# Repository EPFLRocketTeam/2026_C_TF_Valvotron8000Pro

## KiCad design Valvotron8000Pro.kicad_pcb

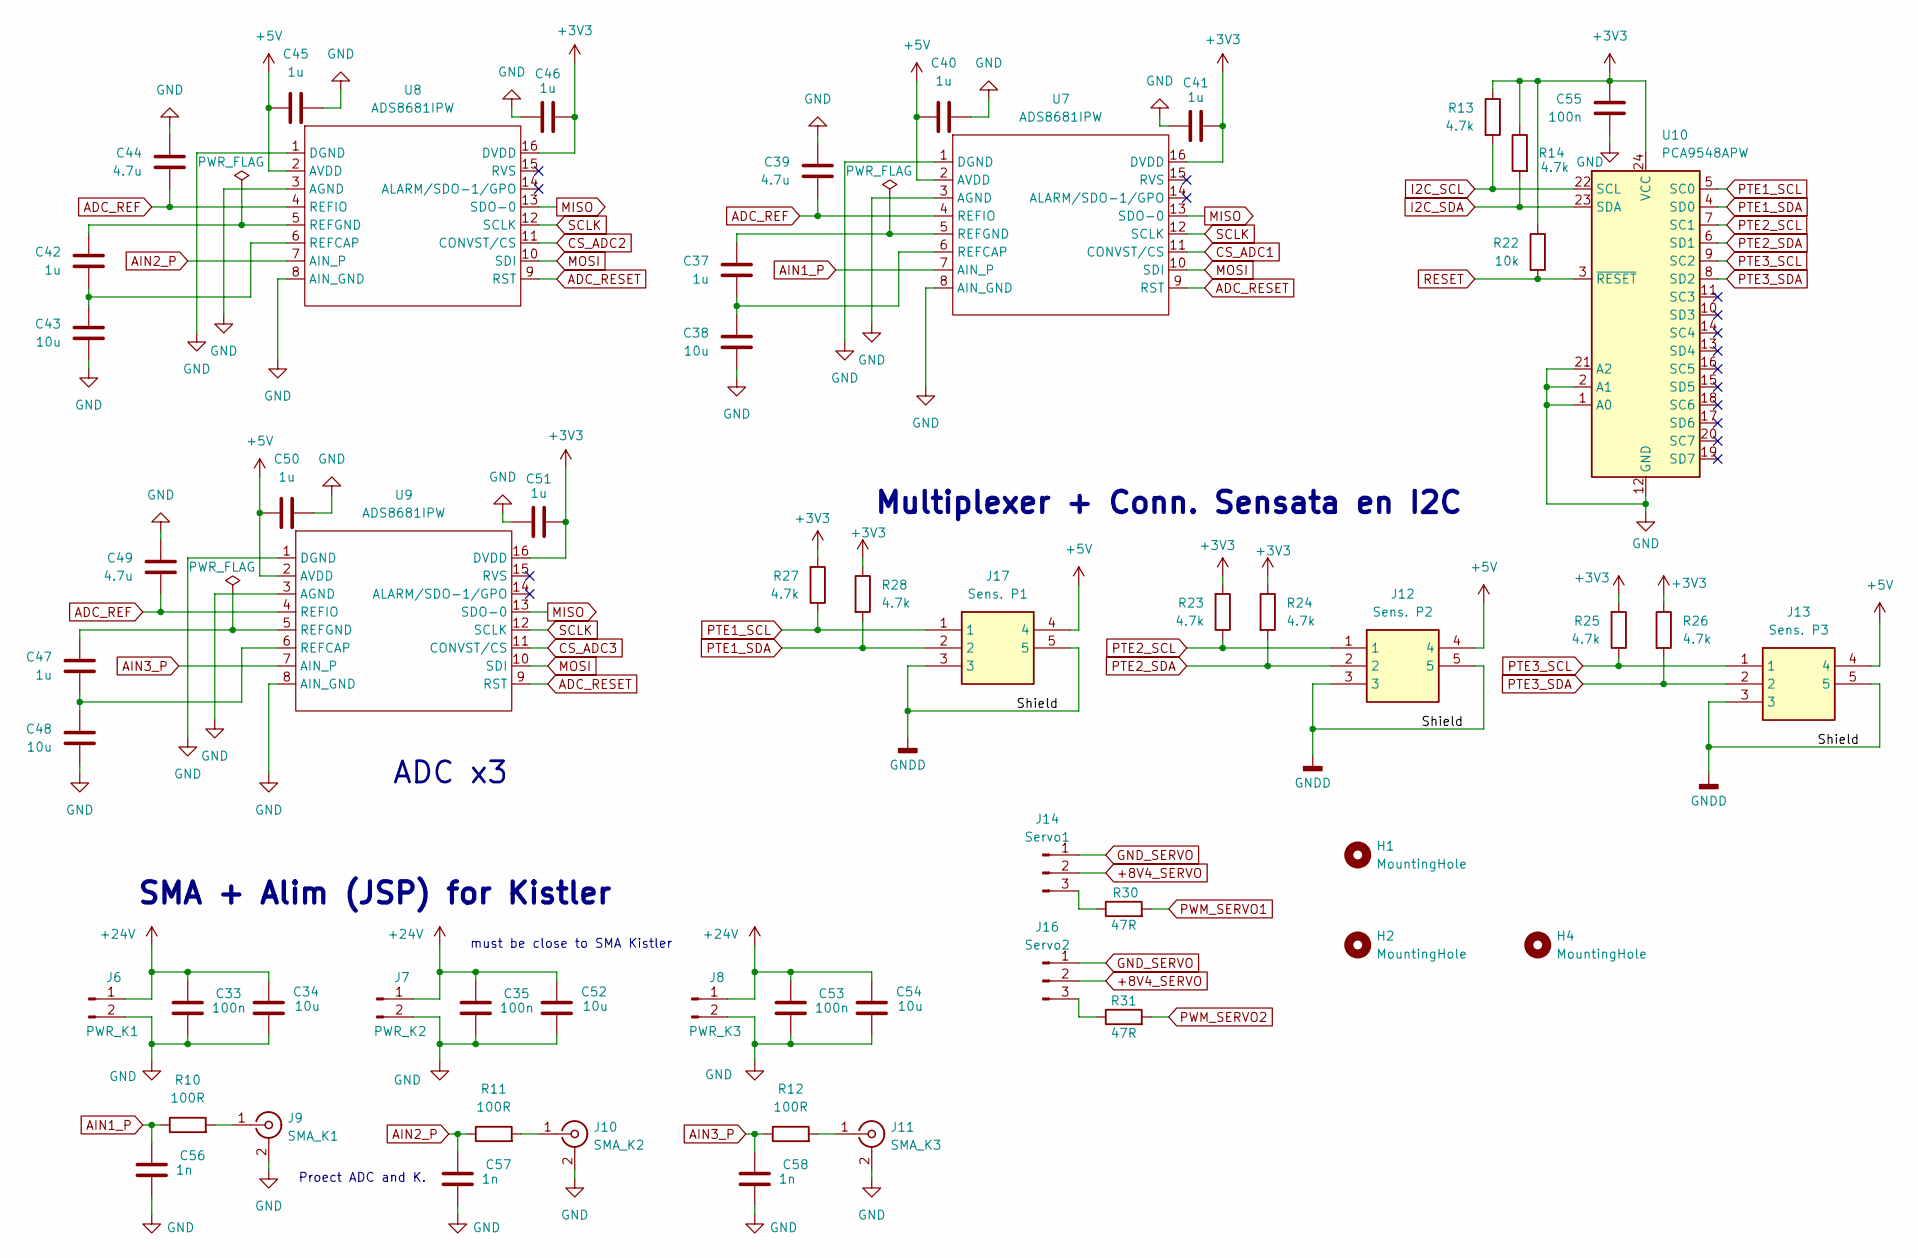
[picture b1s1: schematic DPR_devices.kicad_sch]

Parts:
C33, C35, C53, C55: 100n; C_0402_1005Metric
C34, C52, C54: 10u; C_0805_2012Metric
C37, C40, C41, C42, C45, C46, C47, C50, C51: 1u; C_0402_1005Metric
C38, C43, C48: 10u; C_0603_1608Metric
C39, C44, C49: 4.7u; C_0603_1608Metric
C56, C57, C58: 1n; C_0603_1608Metric
H1, H2, H4: MountingHole; MountingHole_2.5mm
J6: PWR_K1; JST_XH_B2B-XH-AM_1x02_P2.50mm_Vertical
J7: PWR_K2; JST_XH_B2B-XH-AM_1x02_P2.50mm_Vertical
J8: PWR_K3; JST_XH_B2B-XH-AM_1x02_P2.50mm_Vertical
J9: SMA_K1; SMA_Amphenol_901-144_Vertical
J10: SMA_K2; SMA_Amphenol_901-144_Vertical
J11: SMA_K3; SMA_Amphenol_901-144_Vertical
J12: Sens. P2; M12B05PFFREE0001; Manufacturer_Part_Number M12B-05PFFR-EE0001; Mouser Part Number 523-M12B05PFFREE0001
J13: Sens. P3; M12B05PFFREE0001; Manufacturer_Part_Number M12B-05PFFR-EE0001; Mouser Part Number 523-M12B05PFFREE0001
J14: Servo1; PhoenixContact_MSTBVA_2,5_3-G_1x03_P5.00mm_Vertical
J16: Servo2; PhoenixContact_MSTBVA_2,5_3-G_1x03_P5.00mm_Vertical
J17: Sens. P1; M12B05PFFREE0001; Manufacturer_Part_Number M12B-05PFFR-EE0001; Mouser Part Number 523-M12B05PFFREE0001
R10, R11, R12: 100R; R_0603_1608Metric
R13, R14, R23, R24, R25, R26, R27, R28: 4.7k; R_0603_1608Metric
R22: 10k; R_0603_1608Metric
R30, R31: 47R; R_0603_1608Metric
U7, U8, U9: ADS8681IPW; TSSOP-16_4.4x5mm_P0.65mm
U10: PCA9548APW; TSSOP-24_4.4x7.8mm_P0.65mm

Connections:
+3V3: C41.2, C46.2, C51.2, C55.2, R13.1, R14.1, R22.1, R23.2, R24.1, R25.2, R26.1, R27.2, R28.1, U7.16 (DVDD), U8.16 (DVDD), U9.16 (DVDD), U10.24 (VCC); also elsewhere on the board
+8V4_SERVO: J14.2, J16.2; also elsewhere on the board
+24V: C33.1, C34.1, C35.1, C52.1, C53.1, C54.1, J6.1, J7.1, J8.1; also elsewhere on the board
ADC_REF: C39.1, C44.1, C49.1, U7.4 (REFIO), U8.4 (REFIO), U9.4 (REFIO)
ADC_RESET: U7.9 (RST), U8.9 (RST), U9.9 (RST); also elsewhere on the board
AIN1_P: C56.1, R10.1, U7.7 (AIN_P)
AIN2_P: C57.1, R11.1, U8.7 (AIN_P)
AIN3_P: C58.1, R12.1, U9.7 (AIN_P)
CS_ADC1: U7.11 (CONVST/CS); also elsewhere on the board
CS_ADC2: U8.11 (CONVST/CS); also elsewhere on the board
CS_ADC3: U9.11 (CONVST/CS); also elsewhere on the board
GND_SERVO: J14.1, J16.1; also elsewhere on the board
I2C_SCL: R13.2, U10.22 (SCL); also elsewhere on the board
I2C_SDA: R14.2, U10.23 (SDA); also elsewhere on the board
MISO: U7.13 (SDO-0), U8.13 (SDO-0), U9.13 (SDO-0); also elsewhere on the board
MOSI: U7.10 (SDI), U8.10 (SDI), U9.10 (SDI); also elsewhere on the board
unnamed: J9.1 (In), R10.2
unnamed: J10.1 (In), R11.2
unnamed: J11.1 (In), R12.2
unnamed: J14.3, R30.1
unnamed: J16.3, R31.1
unnamed: C37.1, C38.2, U7.6 (REFCAP)
unnamed: C37.2, U7.5 (REFGND)
unnamed: C42.1, C43.2, U8.6 (REFCAP)
unnamed: C42.2, U8.5 (REFGND)
unnamed: C47.1, C48.2, U9.6 (REFCAP)
unnamed: C47.2, U9.5 (REFGND)
PTE1_SCL: J17.1, R27.1, U10.5 (SC0)
PTE1_SDA: J17.2, R28.2, U10.4 (SD0)
PTE2_SCL: J12.1, R23.1, U10.7 (SC1)
PTE2_SDA: J12.2, R24.2, U10.6 (SD1)
PTE3_SCL: J13.1, R25.1, U10.9 (SC2)
PTE3_SDA: J13.2, R26.2, U10.8 (SD2)
PWM_SERVO1: R30.2; also elsewhere on the board
PWM_SERVO2: R31.2; also elsewhere on the board
RESET: R22.2, U10.3 (~RESET); also elsewhere on the board
SCLK: U7.12 (SCLK), U8.12 (SCLK), U9.12 (SCLK); also elsewhere on the board

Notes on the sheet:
ADC x3
SMA + Alim (JSP) for Kistler
Multiplexer + Conn. Sensata en I2C
must be close to SMA Kistler
Proect ADC and K.

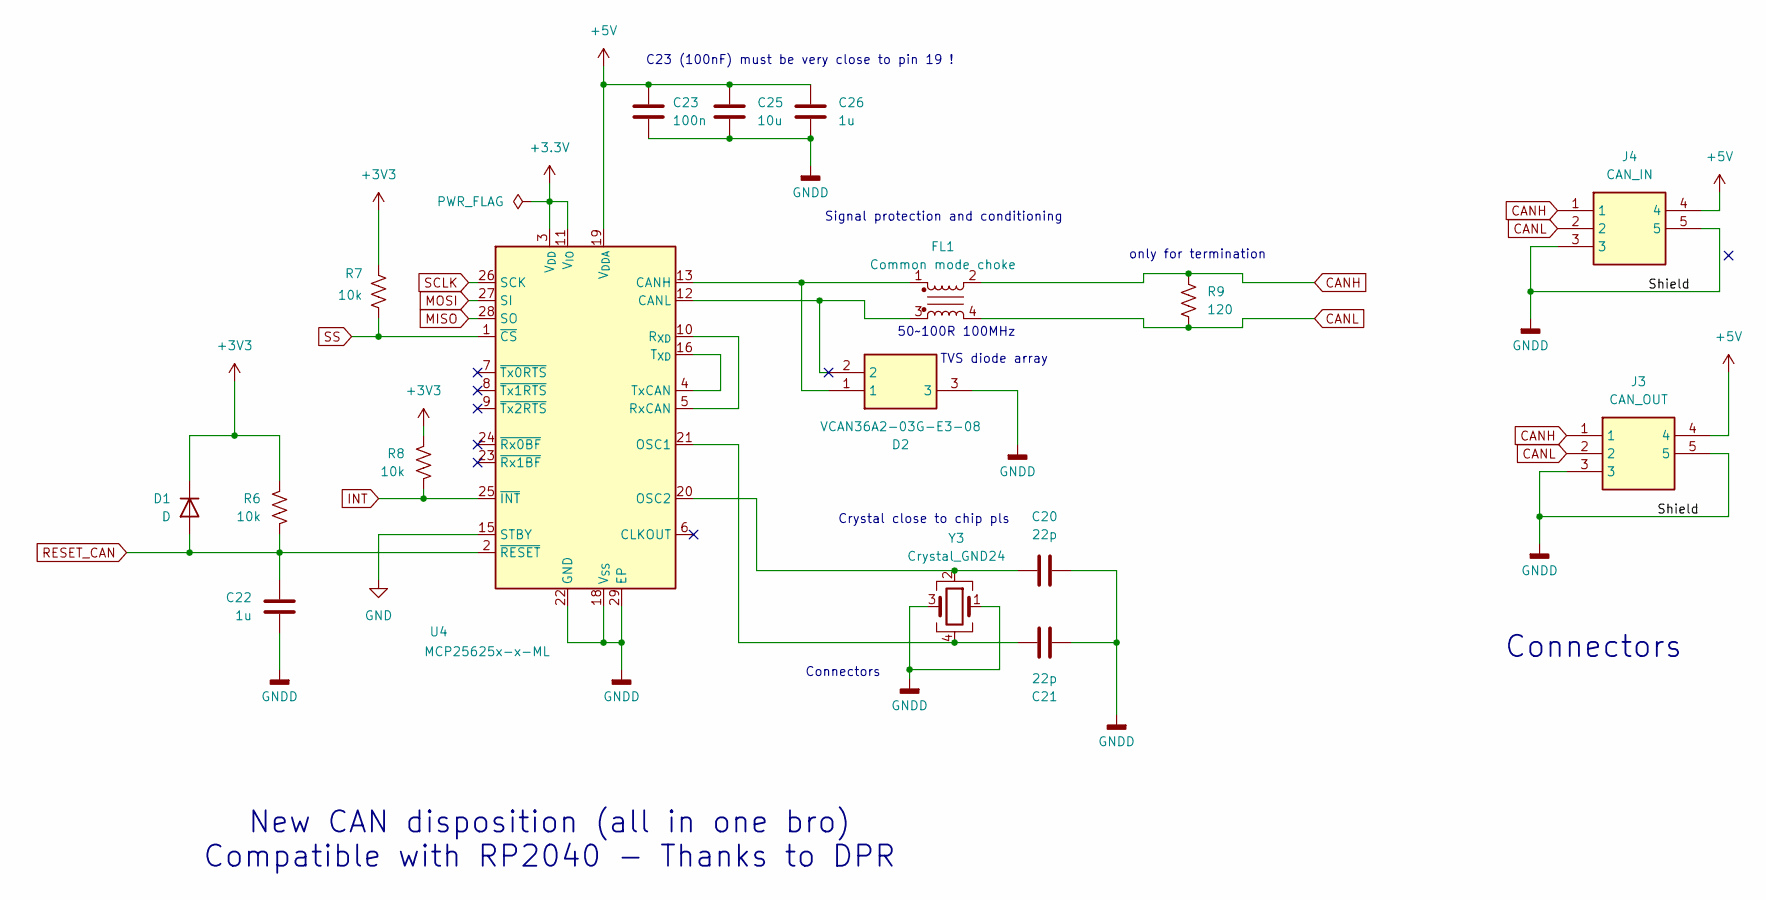
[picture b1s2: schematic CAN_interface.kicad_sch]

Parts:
C20, C21: 22p; C_0603_1608Metric
C22, C26: 1u; C_0603_1608Metric
C23: 100n; C_0402_1005Metric
C25: 10u; C_0805_2012Metric
D1: D; D_SOD-123
D2: VCAN36A2-03G-E3-08; SOT65P230X110-3N; Manufacturer_Part_Number VCAN36A2-03G-E3-08; Mouser Part Number 78-VCAN36A203G-E3-08
FL1: Common mode choke; DLW21SN121HQ2L
J3: CAN_OUT; M12B05PFFREE0001; Manufacturer_Part_Number M12B-05PFFR-EE0001; Mouser Part Number 523-M12B05PFFREE0001
J4: CAN_IN; M12B05PFFREE0001; Manufacturer_Part_Number M12B-05PFFR-EE0001; Mouser Part Number 523-M12B05PFFREE0001
R6, R7, R8: 10k; R_0603_1608Metric
R9: 120; R_0603_1608Metric
U4: MCP25625x-x-ML; QFN-28-1EP_6x6mm_P0.65mm_EP4.25x4.25mm
Y3: Crystal_GND24; Crystal_SMD_3225-4Pin_3.2x2.5mm

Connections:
+3.3V: U4.3 (V_{DD}), U4.11 (V_{IO})
+3V3: D1.1 (K), R6.1, R7.1, R8.1; also elsewhere on the board
CANH: FL1.2, J3.1, J4.1, R9.1
CANL: FL1.4, J3.2, J4.2, R9.2
INT: R8.2, U4.25 (~INT); also elsewhere on the board
MISO: U4.28 (SO); also elsewhere on the board
MOSI: U4.27 (SI); also elsewhere on the board
unnamed: D2.1, FL1.1, U4.13 (CANH)
unnamed: C21.1, U4.21 (OSC1), Y3.4
unnamed: C20.1, U4.20 (OSC2), Y3.2
unnamed: U4.5 (RxCAN), U4.10 (R_{XD})
unnamed: U4.4 (TxCAN), U4.16 (T_{XD})
RESET_CAN: C22.1, D1.2 (A), R6.2, U4.2 (~RESET); also elsewhere on the board
SCLK: U4.26 (SCK); also elsewhere on the board
SS: R7.2, U4.1 (~CS); also elsewhere on the board

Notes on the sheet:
Connectors
Crystal close to chip pls
TVS diode array
only for termination
Signal protection and conditioning
50~100R 100MHz
New CAN disposition (all in one bro) Compatible with RP2040 - Thanks to DPR
C23 (100nF) must be very close to pin 19 !

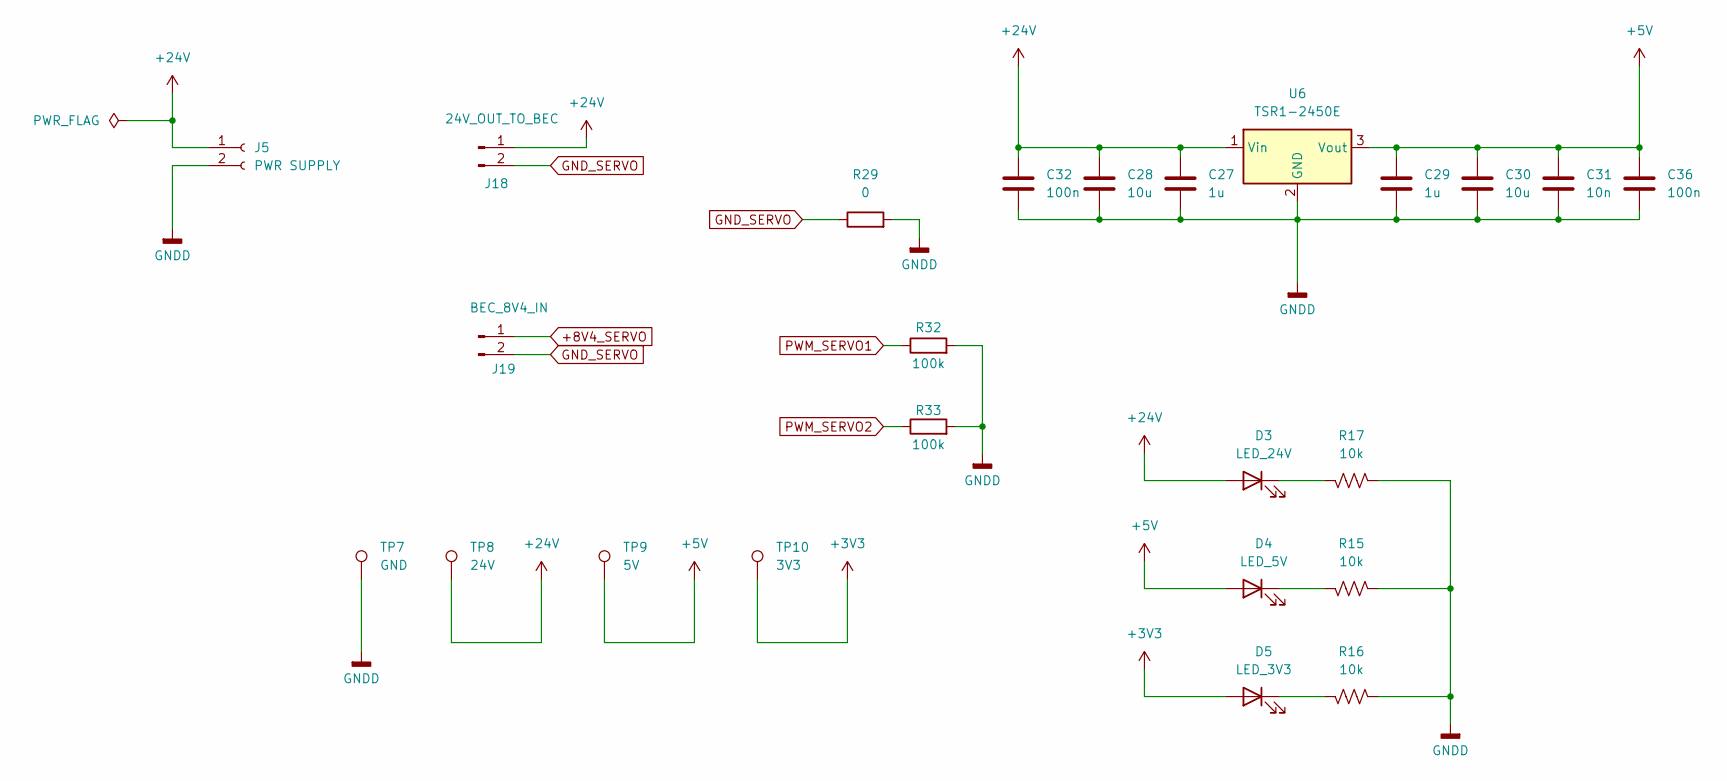
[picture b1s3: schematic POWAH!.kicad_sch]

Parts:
C27, C29: 1u; C_0603_1608Metric
C28, C30: 10u; C_0805_2012Metric
C31: 10n; C_0402_1005Metric
C32, C36: 100n; C_0402_1005Metric
D3: LED_24V; LED_0805_2012Metric
D4: LED_5V; LED_0805_2012Metric
D5: LED_3V3; LED_0805_2012Metric
J5: PWR SUPPLY; AMASS_XT30U-F_1x02_P5.0mm_Vertical
J18: 24V_OUT_TO_BEC; AMASS_XT30U-F_1x02_P5.0mm_Vertical
J19: BEC_8V4_IN; AMASS_XT30U-F_1x02_P5.0mm_Vertical
R15, R16, R17: 10k; R_0603_1608Metric
R29: 0; R_0805_2012Metric
R32, R33: 100k; R_0603_1608Metric
TP7: GND; TestPoint_Pad_D2.0mm
TP8: 24V; TestPoint_Pad_D2.0mm
TP9: 5V; TestPoint_Pad_D2.0mm
TP10: 3V3; TestPoint_Pad_D2.0mm
U6: TSR1-2450E; Converter_DCDC_TRACO_TSR1-xxxxE_THT

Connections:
+3V3: D5.2 (A); also elsewhere on the board
+8V4_SERVO: J19.1; also elsewhere on the board
+24V: C27.1, C28.1, C32.1, D3.2 (A), J5.1, J18.1, U6.1 (Vin); also elsewhere on the board
GND_SERVO: J18.2, J19.2, R29.1; also elsewhere on the board
unnamed: D3.1 (K), R17.1
unnamed: D4.1 (K), R15.1
unnamed: D5.1 (K), R16.1
PWM_SERVO1: R32.1; also elsewhere on the board
PWM_SERVO2: R33.1; also elsewhere on the board

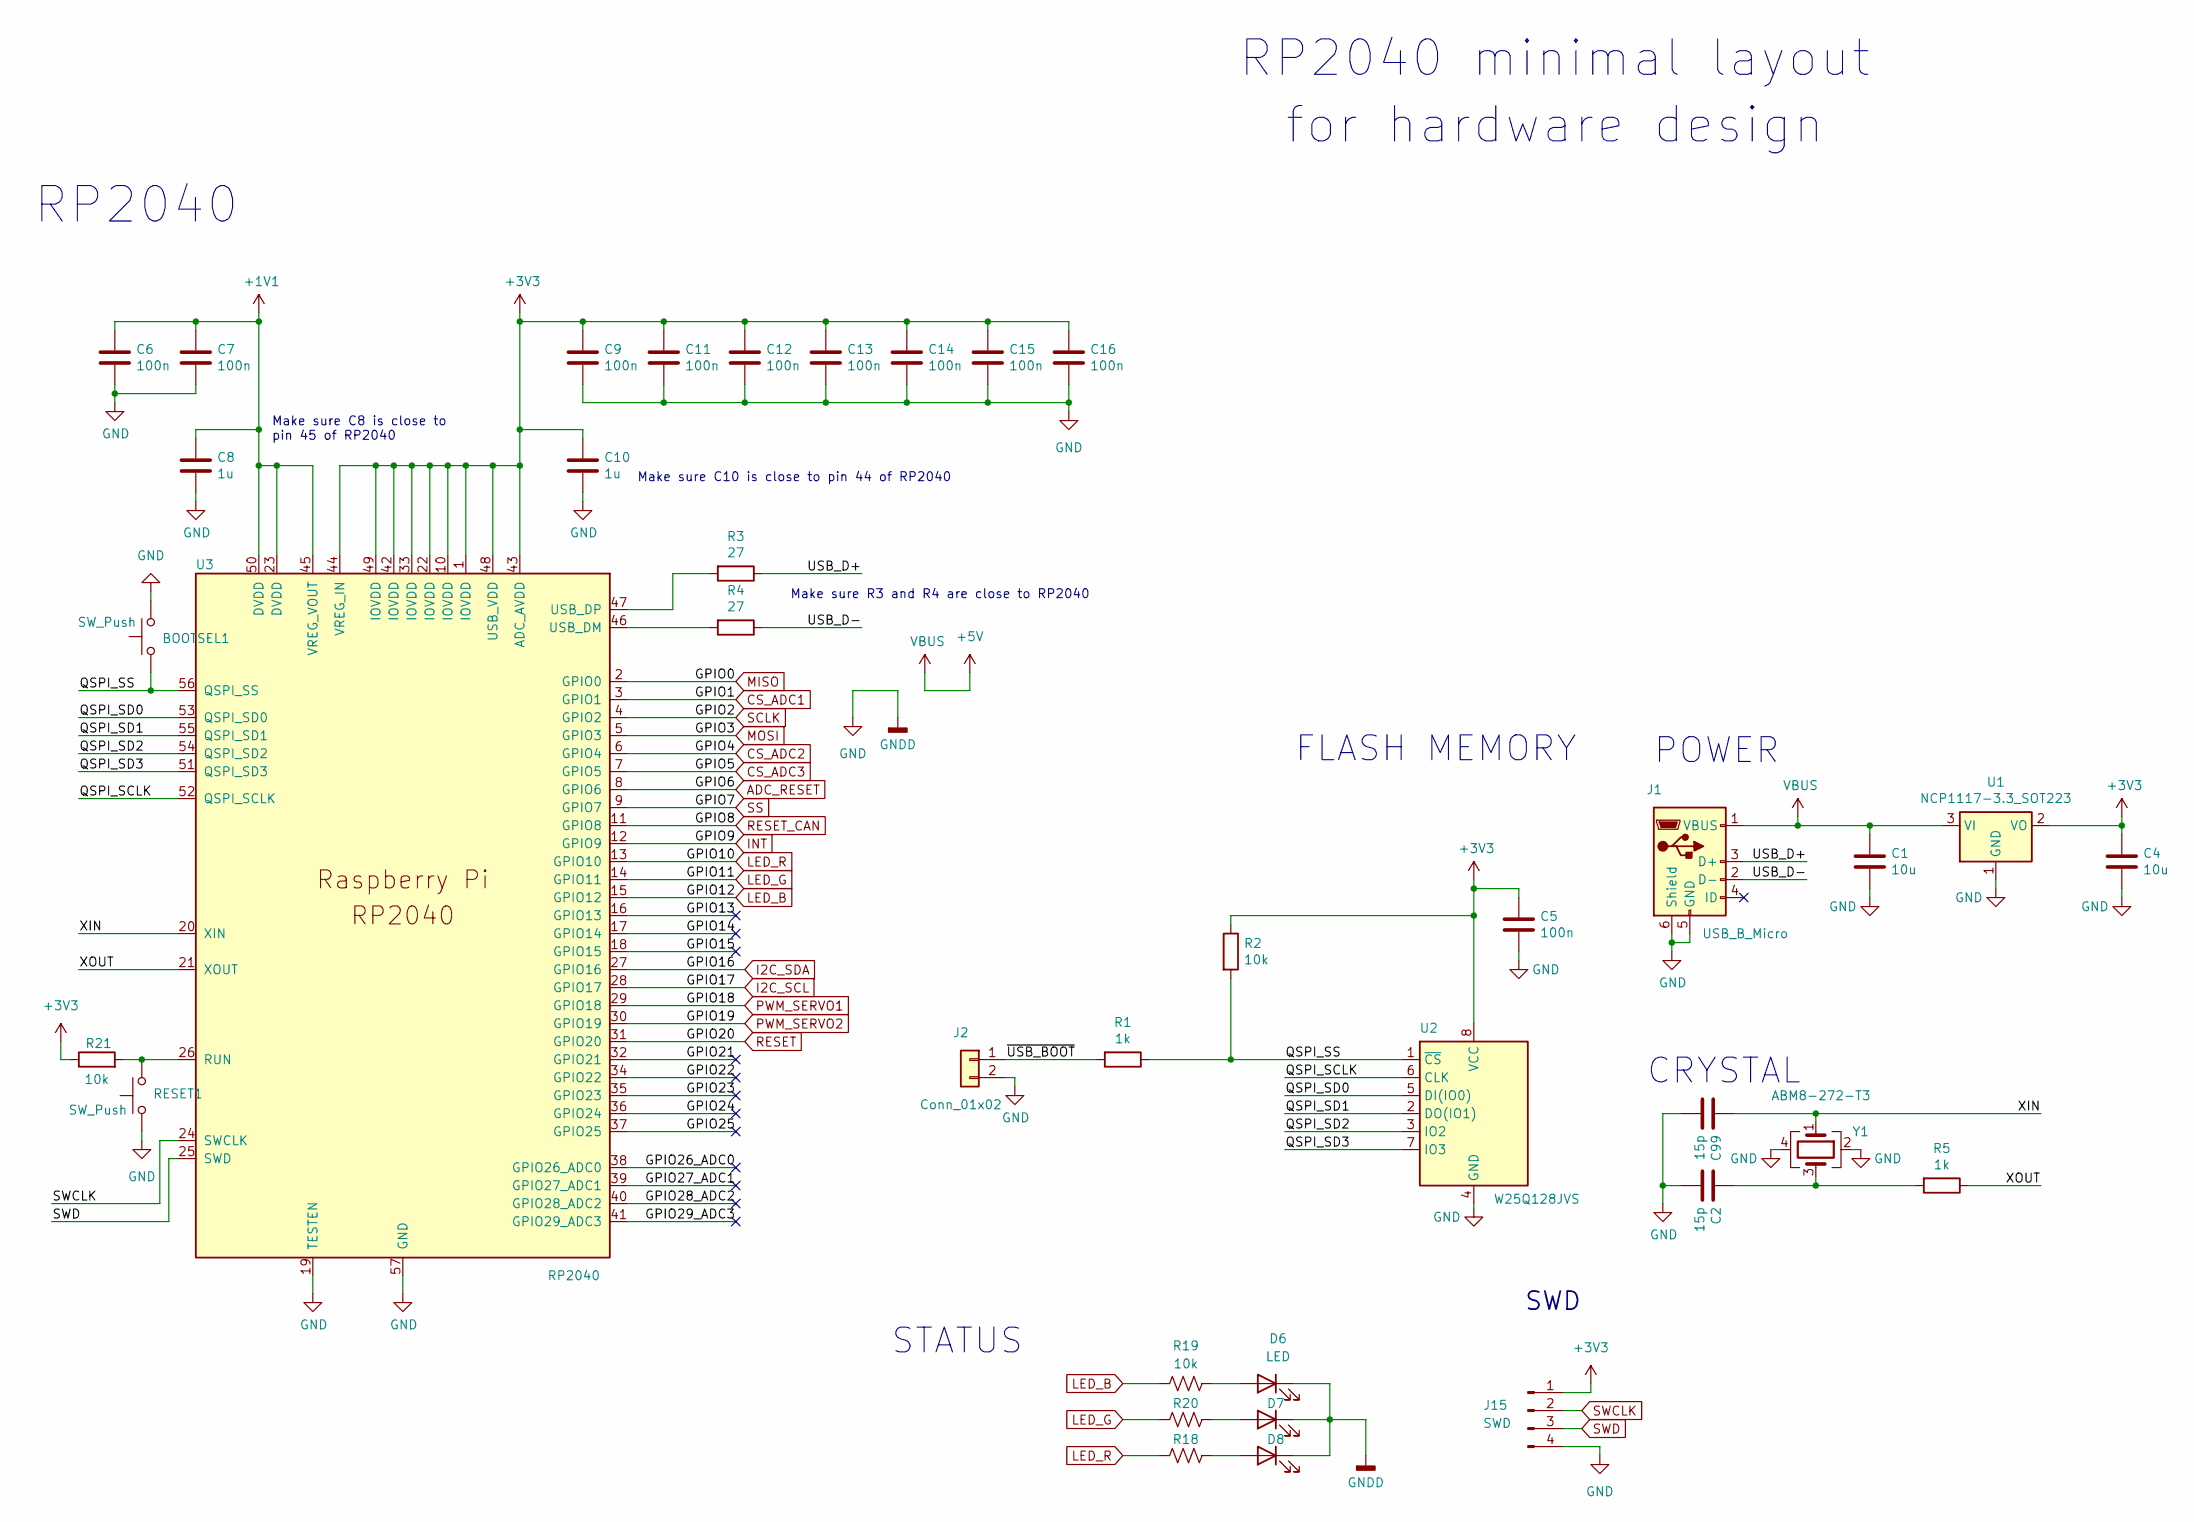
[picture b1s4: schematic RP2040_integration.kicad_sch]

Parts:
BOOTSEL1: SW_Push; SW_SPST_B3U-1000P
C1, C4: 10u; C_0805_2012Metric
C2, C99: 15p; C_0805_2012Metric
C5, C6, C7, C9, C11, C12, C13, C14, C15, C16: 100n; C_0402_1005Metric
C8, C10: 1u; C_0603_1608Metric
D6, D7, D8: LED; LED_0805_2012Metric
J1: USB_B_Micro; USB_Micro-B_Amphenol_10103594-0001LF_Horizontal_modified
J2: Conn_01x02; PinHeader_1x02_P2.54mm_Vertical
J15: SWD; PinHeader_1x04_P2.54mm_Vertical
R1, R5: 1k; R_0603_1608Metric
R2, R18, R19, R20, R21: 10k; R_0603_1608Metric
R3, R4: 27; R_0603_1608Metric
RESET1: SW_Push; SW_SPST_B3U-1000P
U1: NCP1117-3.3_SOT223; SOT-223-3_TabPin2
U2: W25Q128JVS; SOIC-8_5.3x5.3mm_P1.27mm
U3: RP2040; RP2040-QFN-56
Y1: ABM8-272-T3; Crystal_SMD_3225-4Pin_3.2x2.5mm

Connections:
+1V1: C6.1, C7.1, C8.1, U3.23 (DVDD), U3.45 (VREG_VOUT), U3.50 (DVDD)
+3V3: C4.1, C5.1, C9.1, C10.1, C11.1, C12.1, C13.1, C14.1, C15.1, C16.1, J15.1, R2.1, R21.1, U1.2 (VO), U2.8 (VCC), U3.1 (IOVDD), U3.10 (IOVDD), U3.22 (IOVDD), U3.33 (IOVDD), U3.42 (IOVDD), U3.43 (ADC_AVDD), U3.44 (VREG_IN), U3.48 (USB_VDD), U3.49 (IOVDD); also elsewhere on the board
/RP2040_integration/GPIO13: U3.16 (GPIO13)
/RP2040_integration/GPIO14: U3.17 (GPIO14)
/RP2040_integration/GPIO15: U3.18 (GPIO15)
/RP2040_integration/GPIO21: U3.32 (GPIO21)
/RP2040_integration/GPIO22: U3.34 (GPIO22)
/RP2040_integration/GPIO23: U3.35 (GPIO23)
/RP2040_integration/GPIO24: U3.36 (GPIO24)
/RP2040_integration/GPIO25: U3.37 (GPIO25)
/RP2040_integration/GPIO26_ADC0: U3.38 (GPIO26_ADC0)
/RP2040_integration/GPIO27_ADC1: U3.39 (GPIO27_ADC1)
/RP2040_integration/GPIO28_ADC2: U3.40 (GPIO28_ADC2)
/RP2040_integration/GPIO29_ADC3: U3.41 (GPIO29_ADC3)
/RP2040_integration/QSPI_SCLK: U2.6 (CLK), U3.52 (QSPI_SCLK)
/RP2040_integration/QSPI_SD0: U2.5 (DI(IO0)), U3.53 (QSPI_SD0)
/RP2040_integration/QSPI_SD1: U2.2 (DO(IO1)), U3.55 (QSPI_SD1)
/RP2040_integration/QSPI_SD2: U2.3 (IO2), U3.54 (QSPI_SD2)
/RP2040_integration/QSPI_SD3: U2.7 (IO3), U3.51 (QSPI_SD3)
/RP2040_integration/QSPI_SS: BOOTSEL1.2, R1.1, R2.2, U2.1 (~CS), U3.56 (QSPI_SS)
/RP2040_integration/USB_D+: J1.3 (D+), R3.1
/RP2040_integration/XIN: C99.1, U3.20 (XIN), Y1.1
/RP2040_integration/XOUT: R5.1, U3.21 (XOUT)
ADC_RESET: U3.8 (GPIO6); also elsewhere on the board
CS_ADC1: U3.3 (GPIO1); also elsewhere on the board
CS_ADC2: U3.6 (GPIO4); also elsewhere on the board
CS_ADC3: U3.7 (GPIO5); also elsewhere on the board
I2C_SCL: U3.28 (GPIO17); also elsewhere on the board
I2C_SDA: U3.27 (GPIO16); also elsewhere on the board
INT: U3.12 (GPIO9); also elsewhere on the board
LED_B: R19.2, U3.15 (GPIO12)
LED_G: R20.2, U3.14 (GPIO11)
LED_R: R18.2, U3.13 (GPIO10)
MISO: U3.2 (GPIO0); also elsewhere on the board
MOSI: U3.5 (GPIO3); also elsewhere on the board
unnamed: C2.1, R5.2, Y1.3
unnamed: D6.2 (A), R19.1
unnamed: D7.2 (A), R20.1
unnamed: D8.2 (A), R18.1
unnamed: R21.2, RESET1.2, U3.26 (RUN)
unnamed: R4.2, U3.46 (USB_DM)
unnamed: R3.2, U3.47 (USB_DP)
PWM_SERVO1: U3.29 (GPIO18); also elsewhere on the board
PWM_SERVO2: U3.30 (GPIO19); also elsewhere on the board
RESET: U3.31 (GPIO20); also elsewhere on the board
RESET_CAN: U3.11 (GPIO8); also elsewhere on the board
SCLK: U3.4 (GPIO2); also elsewhere on the board
SS: U3.9 (GPIO7); also elsewhere on the board
SWCLK: J15.2, U3.24 (SWCLK)
SWD: J15.3, U3.25 (SWD)

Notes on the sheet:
Make sure R3 and R4 are close to RP2040
for hardware design
RP2040 minimal layout
FLASH MEMORY
SWD
CRYSTAL
POWER
STATUS
Make sure C10 is close to pin 44 of RP2040
RP2040
Make sure C8 is close to pin 45 of RP2040

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
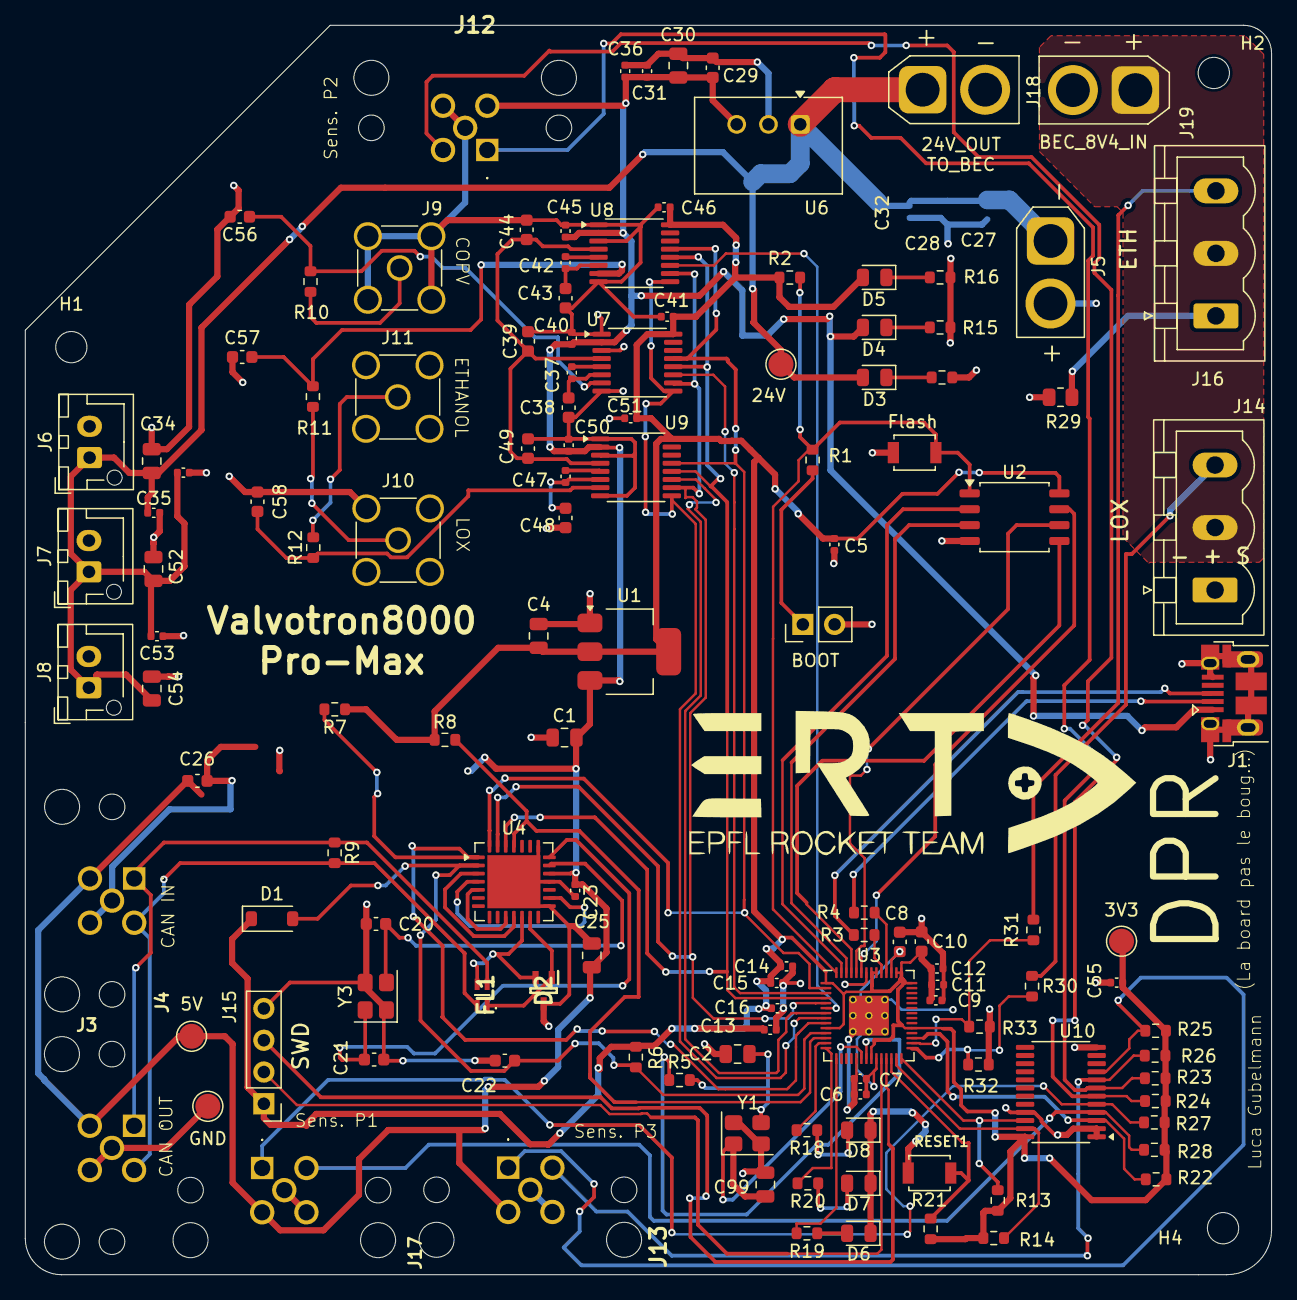
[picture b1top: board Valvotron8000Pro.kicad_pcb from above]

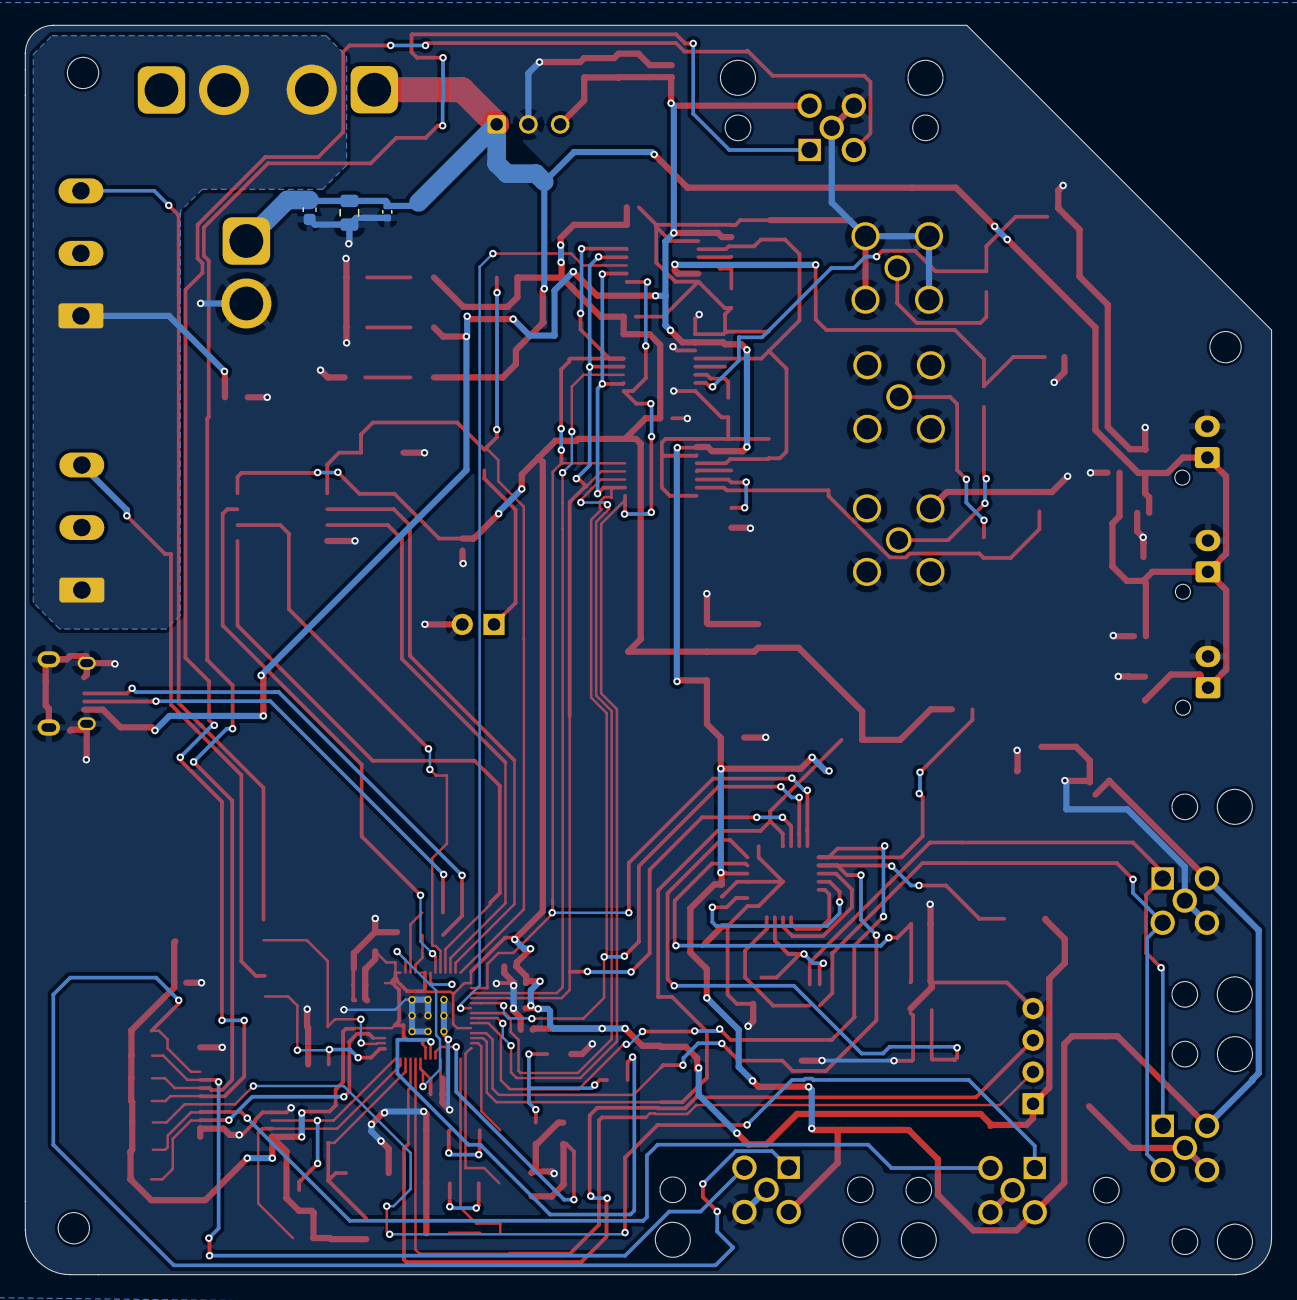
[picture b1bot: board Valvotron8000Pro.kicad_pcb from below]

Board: 2 copper layers, 99.7 x 99.9 mm, 135 parts (3 on the bottom side), 77 nets.

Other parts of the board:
3V3: 3V3; TestPoint_Pad_D2.0mm
5V: 5V; TestPoint_Pad_D2.0mm
24V: 24V; TestPoint_Pad_D2.0mm
BOOT: Conn_01x02; PinHeader_1x02_P2.54mm_Vertical
GND: GND; TestPoint_Pad_D2.0mm

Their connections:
+3V3: 3V3.1; also elsewhere on the board
+24V: 24V.1; also elsewhere on the board

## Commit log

2026-02-23 added libraries
2026-02-24 Added all 3 ADC and routed them to RP2040 !
2026-02-26 Last CPR_devices changes
2026-02-26 Schematic ok (je crois)
2026-02-28 Last Push pour que tu check, après je commence le Layout
2026-03-04 Finito je te laisse check
2026-03-06 added silkscreen indicator for software
2026-03-06 added reset and bootsel buttons
2026-03-09 last modifications
2026-03-10 Changed M12 for SMA + 2 pins alim. --> we will have to split the cable from Kistlers
2026-03-16 Dernières modifs
2026-03-21 Changement des connecteurs servo (ne tenaient pas le courant en pics (=5A)) ++
2026-03-27 changed the mcp - potentiellement final version
2026-03-28 Layout done, pcb ready (finally)
